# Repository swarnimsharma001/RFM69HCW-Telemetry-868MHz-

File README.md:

# RFM69HCW-Telemetry-868MHz-
This project implements a long-range wireless RTK correction data link using RFM69HCW RF module and STM32F103C6T6 microcontroller.

The system reads RTK correction data (RTCM) from a GPS base station and transmits it wirelessly using the RFM69 radio module. Multiple receiver nodes can receive the correction data and forward it to GPS receivers or flight controllers via UART.

This setup is useful for:-

RTK drone systems

Robotics navigation

Autonomous vehicles

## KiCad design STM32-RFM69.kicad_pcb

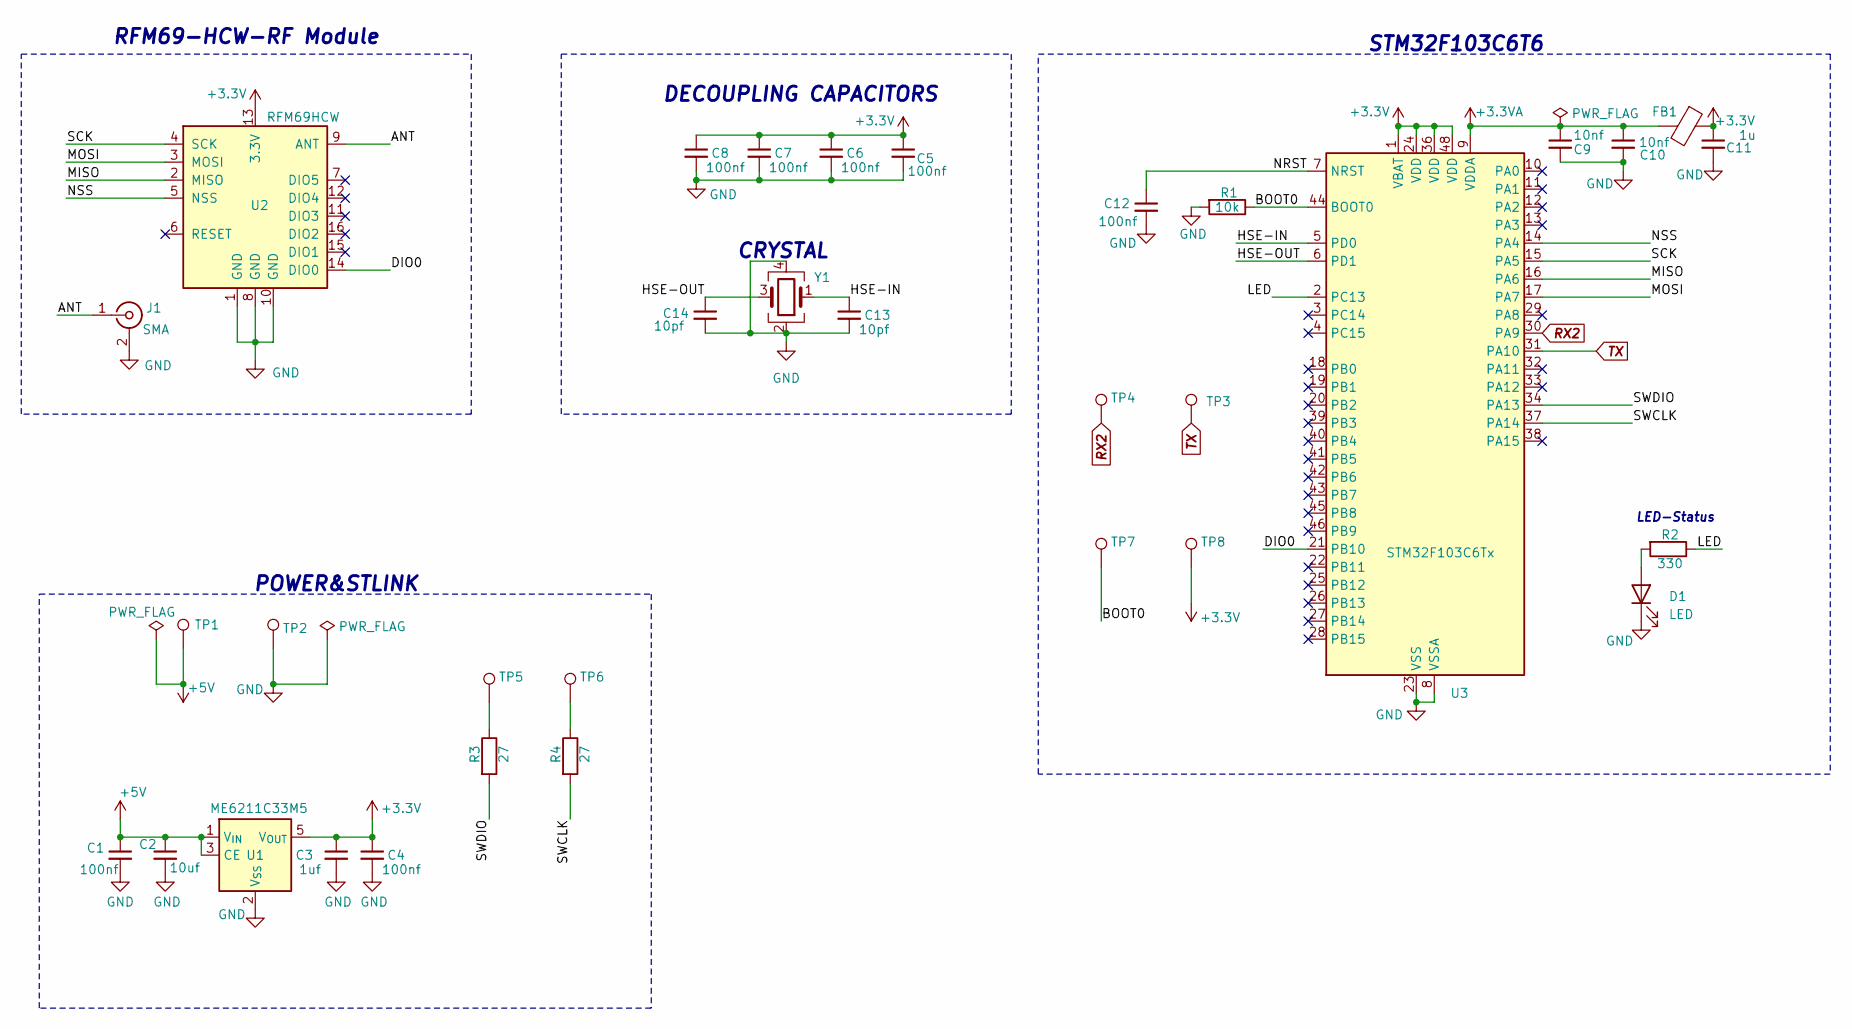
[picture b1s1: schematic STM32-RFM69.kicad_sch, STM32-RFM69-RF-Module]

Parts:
C1: 100nf; C_0603_1608Metric
C2: 10uf; C_0603_1608Metric
C3: 1uf; C_0402_1005Metric
C4, C5, C6, C7, C8, C12: 100nf; C_0402_1005Metric
C9, C10: 10nf; C_0402_1005Metric
C11: 1u; C_0402_1005Metric
C13, C14: 10pf; C_0402_1005Metric
D1: LED; LED_0603_1608Metric
FB1: FerriteBead; L_0603_1608Metric
J1: SMA; U.FL_Hirose_U.FL-R-SMT-1_Vertical
R1: 10k; R_0402_1005Metric
R2: 330; R_0402_1005Metric
R3, R4: 27; R_0402_1005Metric
TP1, TP2, TP3, TP4: TestPoint; PAD mini
TP5, TP6: TestPoint; Circular PAD-hole
TP7, TP8: TestPoint; PAD boot short mini
U1: ME6211C33M5; SOT-23-5
U2: RFM69HCW; HOPERF_RFM9XW_SMD
U3: STM32F103C6Tx; LQFP-48_7x7mm_P0.5mm
Y1: Crystal_GND24; Crystal_SMD_3225-4Pin_3.2x2.5mm 16 mhz

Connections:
+3.3V: C3.1, C4.1, C5.1, C6.1, C7.1, C8.1, C11.1, FB1.1, TP8.1, U1.5 (V_{OUT}), U2.13 (3.3V), U3.1 (VBAT), U3.24 (VDD), U3.36 (VDD), U3.48 (VDD)
+3.3VA: C9.1, C10.1, FB1.2, U3.9 (VDDA)
+5V: C1.1, C2.1, TP1.1, U1.1 (V_{IN}), U1.3 (CE)
/ANT: J1.1 (In), U2.9 (ANT)
/BOOT0: R1.1, TP7.1, U3.44 (BOOT0)
/DIO0: U2.14 (DIO0), U3.21 (PB10)
/HSE-IN: C13.1, U3.5 (PD0), Y1.1
/HSE-OUT: C14.1, U3.6 (PD1), Y1.3
/LED: R2.1, U3.2 (PC13)
/MISO: U2.2 (MISO), U3.16 (PA6)
/MOSI: U2.3 (MOSI), U3.17 (PA7)
/NRST: C12.1, U3.7 (NRST)
/NSS: U2.5 (NSS), U3.14 (PA4)
/SCK: U2.4 (SCK), U3.15 (PA5)
/SWCLK: R4.2, U3.37 (PA14)
/SWDIO: R3.2, U3.34 (PA13)
GND: C1.2, C2.2, C3.2, C4.2, C5.2, C6.2, C7.2, C8.2, C9.2, C10.2, C11.2, C12.2, C13.2, C14.2, D1.1 (K), J1.2 (Ext), R1.2, TP2.1, U1.2 (V_{SS}), U2.1 (GND), U2.8 (GND), U2.10 (GND), U3.8 (VSSA), U3.23 (VSS), U3.35 (VSS), U3.47 (VSS), Y1.2, Y1.4
unnamed: D1.2 (A), R2.2
unnamed: R3.1, TP5.1
unnamed: R4.1, TP6.1
RX2: TP4.1, U3.30 (PA9)
TX: TP3.1, U3.31 (PA10)

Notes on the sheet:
DECOUPLING CAPACITORS
LED-Status
RFM69-HCW-RF Module
STM32F103C6T6
POWER&STLINK
CRYSTAL

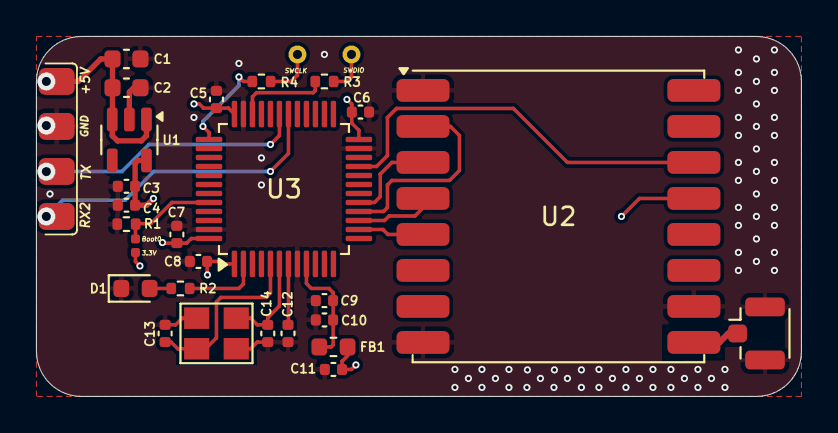
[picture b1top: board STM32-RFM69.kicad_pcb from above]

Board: 4 copper layers, 42.5 x 20.0 mm, 33 parts (0 on the bottom side), 22 nets.

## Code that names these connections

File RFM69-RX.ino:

#include <RFM69.h>
#include <SPI.h>

// UART1 pads for GPS/FC
#define RX_PIN PA10     
#define TX_PIN PA9      
#define BAUD_RATE 9600

// Define the pins for the RFM69
#define RFM69_CS PA4   // NSS pin
#define RFM69_RST PB11  // RESET pin
#define RFM69_IRQ PB10  // IRQ pin

// Built-in LED pin
#define LED_PIN PC13

// RFM69 settings
#define NETWORKID 100
#define MYNODEID 2       // Unique ID for this receiver node (Change for each receiver)
#define FREQUENCY RF69_868MHZ

RFM69 radio(RFM69_CS, RFM69_IRQ, RFM69_RST);

void setup() 
{
  Serial.begin(BAUD_RATE);        // Initialize Serial for debugging
  Serial1.begin(BAUD_RATE);       // Initialize UART1 for (PA9, PA10)
  
  // Initialize SPI and RFM69
  SPI.begin();                    
  radio.initialize(FREQUENCY, MYNODEID, NETWORKID); // Initialize RFM69 radio
  radio.setHighPower();           // Enable high power mode for the RFM69
  radio.encrypt(nullptr);         // Disable encryption

  // Initialize built-in LED pin
  pinMode(LED_PIN, OUTPUT);
  digitalWrite(LED_PIN, HIGH); // Turn off the LED (LED is active low on Bluepill)

  Serial.println("Receiver ready.");
}

void loop() 
{
  if (radio.receiveDone())        // Check if data has been received
  { 
    // Turn on the LED (active low, so LOW turns it on)
    digitalWrite(LED_PIN, LOW);

    // Print received data to Serial and write it to UART1
    for (uint8_t i = 0; i < radio.DATALEN; i++) 
    {
      Serial.print((char)radio.DATA[i]);   // Print received data to Serial for debugging
      Serial1.write((char)radio.DATA[i]);  // Write the received data to UART1
    }

    // Acknowledge receipt of data if acknowledgment is enabled
    if (radio.ACKRequested())
    {
      radio.sendACK();    // Send acknowledgment back to the transmitter
      Serial.println("ACK sent.");
    }

    // Turn off the LED after data is received
    digitalWrite(LED_PIN, HIGH);
  }
}

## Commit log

2026-03-16 Add files via upload
    Kicad PCB File
